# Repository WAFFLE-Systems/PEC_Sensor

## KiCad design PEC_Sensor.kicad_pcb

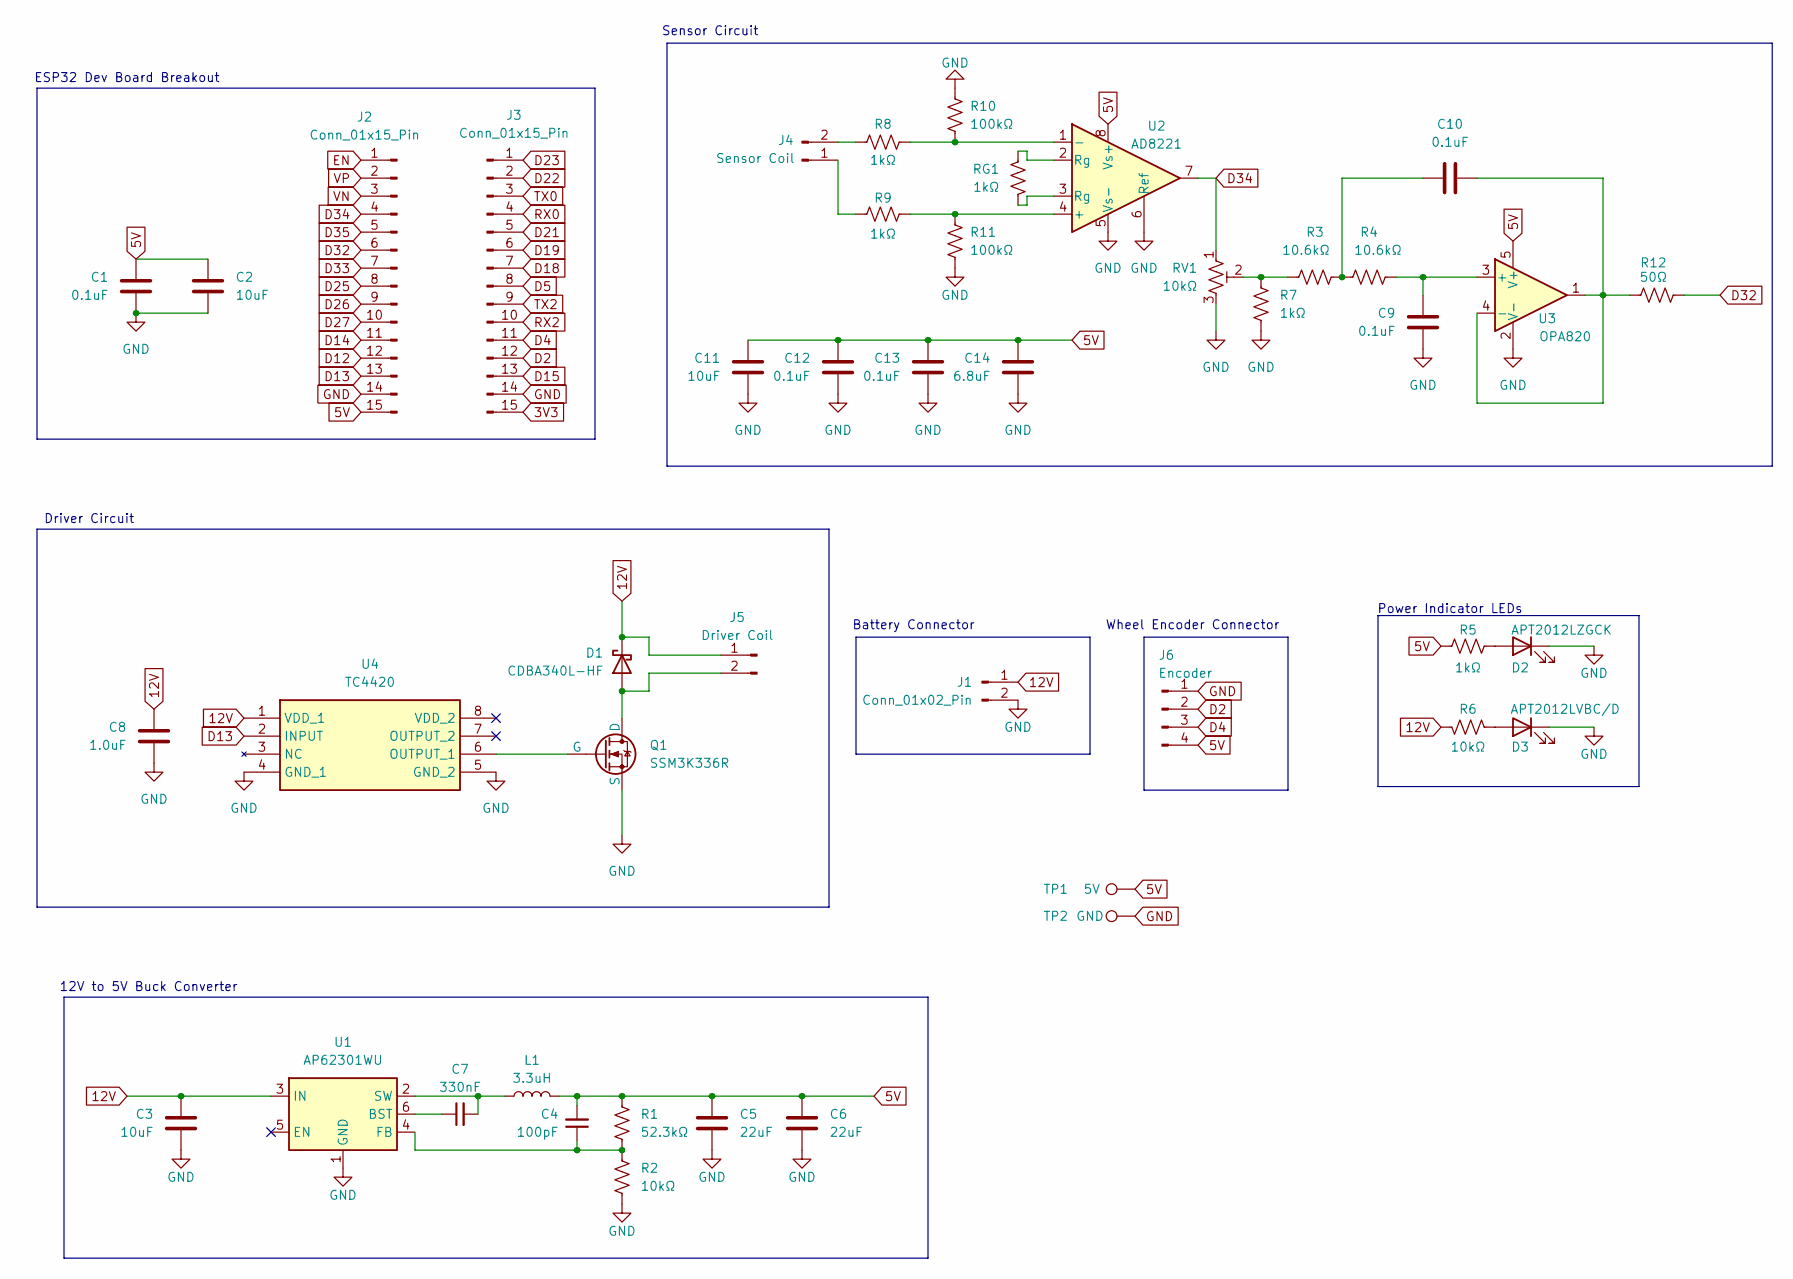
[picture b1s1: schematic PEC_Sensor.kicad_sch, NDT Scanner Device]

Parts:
C1, C9, C10, C12, C13: 0.1uF; C_0603_1608Metric_Pad1.08x0.95mm_HandSolder
C2, C11: 10uF; C_0603_1608Metric_Pad1.08x0.95mm_HandSolder
C3: 10uF; C_0805_2012Metric_Pad1.18x1.45mm_HandSolder
C4: 100pF; C_0603_1608Metric_Pad1.08x0.95mm_HandSolder
C5, C6: 22uF; C_0805_2012Metric_Pad1.18x1.45mm_HandSolder
C7: 330nF; C_0603_1608Metric_Pad1.08x0.95mm_HandSolder
C8: 1.0uF; C_0603_1608Metric_Pad1.08x0.95mm_HandSolder
C14: 6.8uF; C_0603_1608Metric_Pad1.08x0.95mm_HandSolder
D1: CDBA340L-HF; D_SMA_Handsoldering
D2: APT2012LZGCK; LED_0805_2012Metric_Pad1.15x1.40mm_HandSolder
D3: APT2012LVBC/D; LED_0805_2012Metric_Pad1.15x1.40mm_HandSolder
J1: Conn_01x02_Pin; BarrelJack_Horizontal
J2, J3: Conn_01x15_Pin; PinHeader_1x15_P2.54mm_Vertical
J4: Sensor Coil; JST_EH_S2B-EH_1x02_P2.50mm_Horizontal
J5: Driver Coil; JST_EH_S2B-EH_1x02_P2.50mm_Horizontal
J6: Encoder; JST_EH_S4B-EH_1x04_P2.50mm_Horizontal
L1: 3.3uH; L_Taiyo-Yuden_NR-40xx
Q1: SSM3K336R; TSOT-23
R1: 52.3kΩ; R_0603_1608Metric_Pad0.98x0.95mm_HandSolder
R2, R6: 10kΩ; R_0603_1608Metric_Pad0.98x0.95mm_HandSolder
R3, R4: 10.6kΩ; R_0603_1608Metric_Pad0.98x0.95mm_HandSolder
R5, R7, R8, R9: 1kΩ; R_0603_1608Metric_Pad0.98x0.95mm_HandSolder
R10, R11: 100kΩ; R_0603_1608Metric_Pad0.98x0.95mm_HandSolder
R12: 50Ω; R_0603_1608Metric_Pad0.98x0.95mm_HandSolder
RG1: 1kΩ; R_0603_1608Metric_Pad0.98x0.95mm_HandSolder
RV1: 10kΩ; Potentiometer_Bourns_TC33X_Vertical
TP1: 5V; TestPoint_THTPad_D2.0mm_Drill1.0mm
TP2: GND; TestPoint_THTPad_D2.0mm_Drill1.0mm
U1: AP62301WU; TSOT-23-6
U2: AD8221; SOIC-8_3.9x4.9mm_P1.27mm
U3: OPA820; SOT-23-5
U4: TC4420; SOIC-8_3.9x4.9mm_P1.27mm; Mouser Part Number 579-TC4429EOA

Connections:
3V3: J3.15
5V: C1.1, C2.1, C4.2, C5.1, C6.1, C11.2, C12.2, C13.2, C14.2, J2.15, J6.4, L1.2, R1.1, R5.1, TP1.1, U2.8 (Vs+), U3.5 (V+)
12V: C3.1, C8.1, D1.1 (K), J1.1, J5.1, R6.1, U1.3 (IN), U4.1 (VDD_1)
D2: J3.12, J6.2
D4: J3.11, J6.3
D5: J3.8
D12: J2.12
D13: J2.13, U4.2 (INPUT)
D14: J2.11
D15: J3.13
D18: J3.7
D19: J3.6
D21: J3.5
D22: J3.2
D23: J3.1
D25: J2.8
D26: J2.9
D27: J2.10
D32: J2.6, R12.1
D33: J2.7
D34: J2.4, RV1.1, U2.7
D35: J2.5
EN: J2.1
GND: C1.2, C2.2, C3.2, C5.2, C6.2, C8.2, C9.2, C11.1, C12.1, C13.1, C14.1, D2.1 (K), D3.1 (K), J1.2, J2.14, J3.14, J6.1, Q1.2 (S), R2.2, R7.2, R10.2, R11.1, RV1.3, TP2.1, U1.1 (GND), U2.5 (Vs-), U2.6 (Ref), U3.2 (V-), U4.4 (GND_1), U4.5 (GND_2)
unnamed: C10.1, R3.1, R4.2
unnamed: D1.2 (A), J5.2, Q1.3 (D)
unnamed: D2.2 (A), R5.2
unnamed: D3.2 (A), R6.2
unnamed: J4.1, R9.1
unnamed: J4.2, R8.1
unnamed: Q1.1 (G), U4.6 (OUTPUT_1)
unnamed: R3.2, R7.1, RV1.2
unnamed: RG1.1, U2.3 (Rg)
unnamed: RG1.2, U2.2 (Rg)
unnamed: C7.1, U1.6 (BST)
unnamed: C4.1, R1.2, R2.1, U1.4 (FB)
unnamed: C7.2, L1.1, U1.2 (SW)
unnamed: R9.2, R11.2, U2.4 (+)
unnamed: R8.2, R10.1, U2.1 (-)
unnamed: C9.1, R4.1, U3.3 (+)
unnamed: C10.2, R12.2, U3.1, U3.4 (-)
RX0: J3.4
RX2: J3.10
TX0: J3.3
TX2: J3.9
VN: J2.3
VP: J2.2

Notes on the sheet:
Driver Circuit
Sensor Circuit
Wheel Encoder Connector
12V to 5V Buck Converter
Power Indicator LEDs
ESP32 Dev Board Breakout
Battery Connector

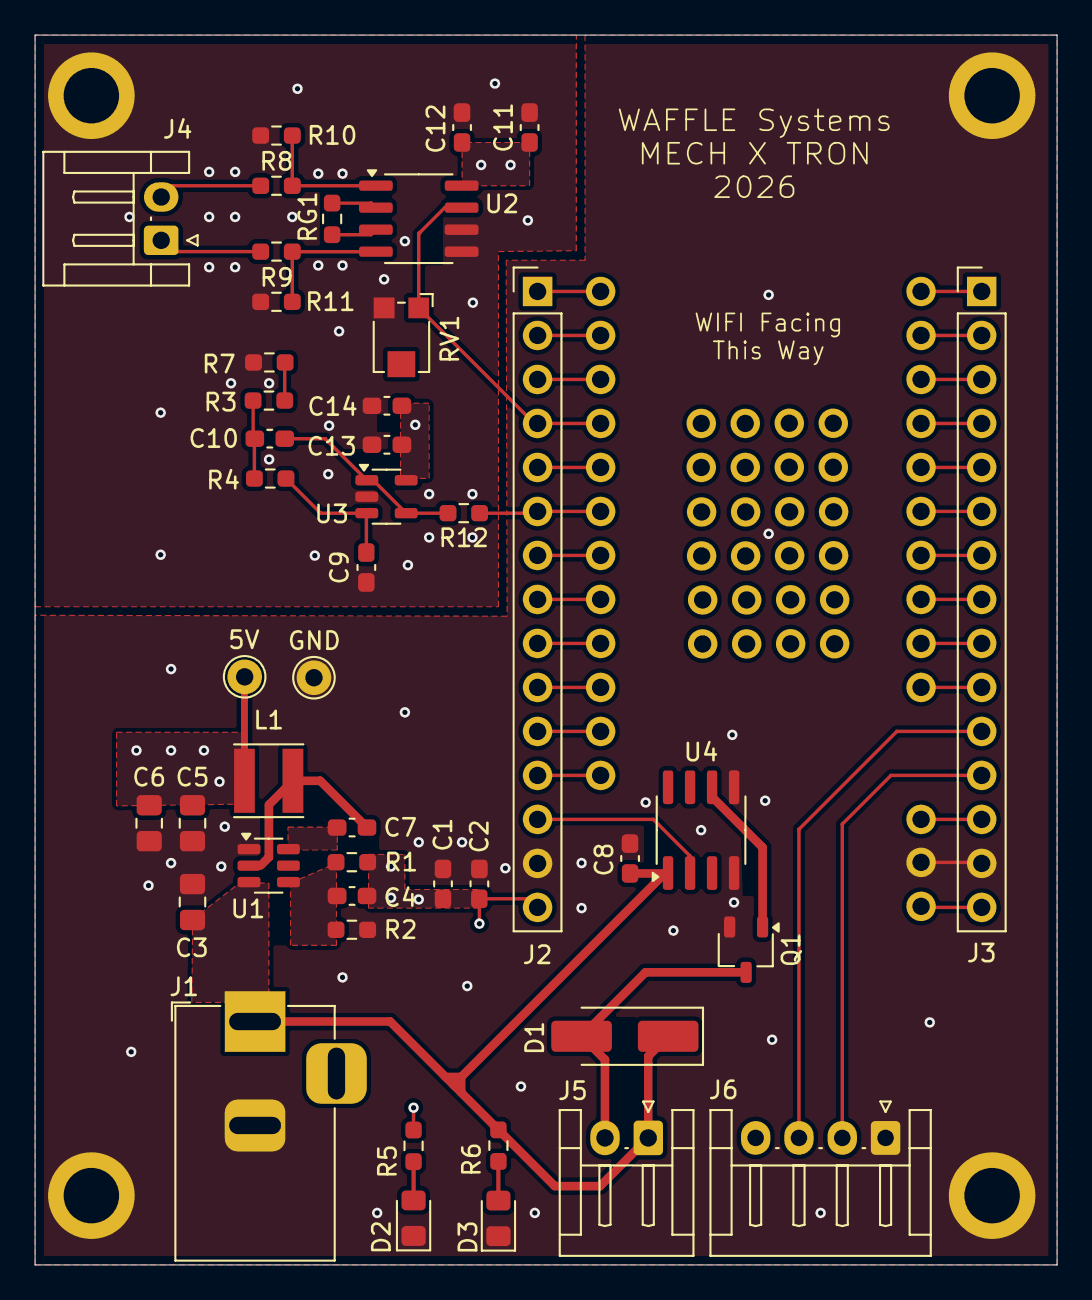
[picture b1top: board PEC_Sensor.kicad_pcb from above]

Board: 4 copper layers, 59.0 x 71.0 mm, 45 parts (0 on the bottom side), 25 nets.

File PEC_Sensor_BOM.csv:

Reference,Quantity,Name,Description,Unit Price,Total,Ratings,Vendor Link,Datasheet
,1,ESP32,ESP32 Dev board,$9.50 ,$9.50 ,"5V, 250mA",https://www.amazon.ca/ELEGOO-ESP-WROOM-32-Development-Blueto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,https://wiki.elegoo.com/oshw-getting-started-kits/first-look-esp32
,1,Battery,12V rechargeable battery,$29.99 ,$29.99 ,"12V, 3000mAh",https://www.amazon.ca/dp/B0DK1JDGXK?ref=ppx_yo2ov_dt_b_fed_a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,
,1,11CEY25F243A,Rotary encoder,$4.07 ,$4.07 ,"5V, 0.5mA",https://www.digikey.ca/en/products/detail/cts-electrocompone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,https://www.ctscorp.com/Files/DataSheets/Encoders/encoders-1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
U2,1,AD8221,Instrumentation amplifier,$11.81 ,$11.81 ,"36V, 0.5nA",https://www.digikey.ca/en/products/detail/analog-devices-inc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,https://www.analog.com/media/en/technical-documentation/data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
U3,1,OPA820,Active filter op amp,$6.11 ,$6.11 ,"5-12V, 5.6mA",https://www.digikey.ca/en/products/detail/texas-instruments/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,https://www.ti.com/lit/ds/symlink/opa820.pdf?HQS=dis-dk-null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
U4,1,TC4420,IC Driver,$2.77 ,$2.77 ,"18V, 6A",https://www.digikey.ca/en/products/detail/microchip-technolo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,https://ww1.microchip.com/downloads/aemDocuments/documents/A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
Q1,1,SSM3K336R,NMOSFET,$0.68 ,$0.68 ,4.5V,https://www.digikey.ca/en/products/detail/toshiba-semiconduc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,https://toshiba.semicon-storage.com/info/SSM3K336R_datasheet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
U1,1,AP62301,Buck converter,$0.55 ,$0.55 ,4.2-12V,https://www.digikey.ca/en/products/detail/diodes-incorporate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,https://www.diodes.com/assets/Datasheets/AP62300_AP62301_AP6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
D1,1,CDBA340L-HF,flyback diode,$1.46 ,$1.46 ,"40V, 3A",https://www.digikey.ca/en/products/detail/comchip-technology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,https://www.comchiptech.com/upload/2026_01_13/12_20260113085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
D2,1,APT2012LZGCK,green LED,$0.80 ,$0.80 ,"2.65V, 2mA",https://www.digikey.ca/en/products/detail/kingbright/APT2012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,https://www.kingbrightusa.com/images/catalog/SPEC/APT2012LZGCK.pdf
D3,1,APT2012LVBC/D,blue LED,$0.80 ,$0.80 ,"2.65V, 2mA",https://www.digikey.ca/en/products/detail/kingbright/APT2012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,https://www.kingbrightusa.com/images/catalog/SPEC/APT2012LVBC-D.pdf
RV1,1,TC33X-2,10kOhm potentiometer,$0.38 ,$0.38 ,"10kOhm, 0.15W",https://www.digikey.ca/en/products/detail/bourns-inc/TC33X-2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,https://www.bourns.com/docs/Product-Datasheets/TC33.pdf
L1,1,NRS4018T3R3MDGJ,3.3uH inductor,$0.26 ,$0.26 ,2A,https://www.digikey.ca/en/products/detail/taiyo-yuden/NRS401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,https://mm.digikey.com/Volume0/opasdata/d220001/medias/docus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
two from board 2,2,,0.01uF Cap,$0.02 ,$0.04 ,0.01uF,,
"C1,C9,C10,C12,C13",5,,0.1uF Cap,$0.02 ,$0.08 ,0.1uF,,
C8,1,,1.0uF Cap,$0.05 ,$0.05 ,1.0uF,,
"C2,C11",2,,"10uF Cap, 0603",$0.15 ,$0.30 ,10uF,,
C3,1,,10uF Cap 0805,$0.32 ,$0.32 ,10uF,,
C14,1,,6.8uF Cap,$0.84 ,$0.84 ,6.8uF,,
"C5,C6",2,,22uF Cap,$0.38 ,$0.76 ,22uF,,
C4,1,,0.1nF Cap,$0.02 ,$0.02 ,0.1nF,,
C7,1,,330nF Cap,$0.32 ,$0.32 ,330nF,,
"R5,R7,R8,R9",4,,1kΩ Res,$0.01 ,$0.04 ,1kΩ,,
"R2,R6,four board 2",6,,10kΩ Res,$0.01 ,$0.05 ,10kΩ,,
"R10,R11",2,,100kΩ Res,$0.00 ,$0.00 ,100kΩ,,
"R3,R4",2,,10.6kΩ Res,$0.18 ,$0.36 ,10.6kΩ,,
R1,1,,52.3kΩ Res,$0.01 ,$0.01 ,52.3kΩ,,
RG1,1,,470Ω Res,$0.01 ,$0.01 ,470Ω,,
"J1(board 2),J6",2,S4B-EH,JST EH 1x4 pin,$0.19 ,$0.38 ,,https://www.digikey.ca/en/products/detail/jst-sales-america-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,https://www.jst-mfg.com/product/pdf/eng/eEH.pdf
"J4,J5",2,S2B-EH,JST EH 1x2 pin,$0.16 ,$0.32 ,,https://www.digikey.ca/en/products/detail/jst-sales-america-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,https://www.jst-mfg.com/product/pdf/eng/eEH.pdf
"J2,H3",2,Header pin,Female Header 1x15 pin,$0.55 ,$1.10 ,,,
J1,1,PJ-102A,Power jack,$0.88 ,$0.88 ,,https://www.digikey.ca/en/products/detail/same-sky-formerly-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,https://www.sameskydevices.com/product/resource/pj-102a.pdf

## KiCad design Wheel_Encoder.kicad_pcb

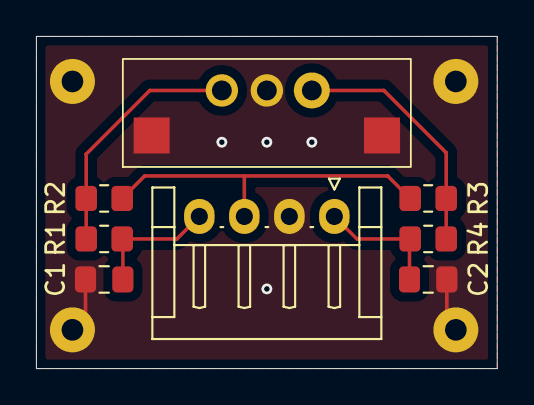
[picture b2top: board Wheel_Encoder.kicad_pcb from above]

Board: 2 copper layers, 25.6 x 18.5 mm, 8 parts (0 on the bottom side), 6 nets.

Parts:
C1, C2: 10nF; C_0805_2012Metric_Pad1.18x1.45mm_HandSolder
EN1: 11CE; RotaryEncoder_CTS_11CE_NoSwitch
J1: Conn_01x04_Pin; JST_EH_S4B-EH_1x04_P2.50mm_Horizontal
R1, R2, R3, R4: 10kΩ; R_0805_2012Metric_Pad1.20x1.40mm_HandSolder

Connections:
/5V: J1.3, R2.2, R3.2
/EnA: C2.1, J1.1, R4.1
/EnB: C1.2, J1.4, R1.2
GND: C1.1, C2.2, EN1.1, EN1.2, EN1.C, J1.2
unnamed: EN1.A, R3.1, R4.2
unnamed: EN1.B, R1.1, R2.1

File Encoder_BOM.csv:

"Reference","Qty","Value","DNP","Exclude from BOM","Exclude from Board","Footprint","Datasheet"
"C1,C2","2","0.01uF","","","","Capacitor_SMD:C_0805_2012Metric_Pad1.18x1.45mm_HandSolder","~"
"EN1","1","11CE","","","","11CEY25F243A:RotaryEncoder_CTS_11CE_NoSwitch","~"
"J1","1","Conn_01x04_Pin","","","","Connector_JST:JST_EH_S4B-EH_1x04_P2.50mm_Horizontal","~"
"R1,R2,R3,R4","4","10kΩ","","","","Resistor_SMD:R_0805_2012Metric_Pad1.20x1.40mm_HandSolder","~"

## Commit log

2026-01-14 revised circuits
2026-01-15 revision 2 finished
2026-01-19 fixed gitignore
2026-01-19 oops
2026-01-29 jan 29
2026-02-03 finished footprints
2026-02-03 ignore cache files
2026-02-03 cleaned up repo
2026-02-03 initial
2026-02-16 final design done
2026-02-16 final design
2026-03-04 updated led values
2026-03-09 updated resistor values
2026-03-10 updated BOM
2026-03-24 improved design post symposium
